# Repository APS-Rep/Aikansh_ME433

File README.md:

# Aikansh_ME433
Repository for ME433 Spring 2022 (Aikansh Prakash Shenoy)

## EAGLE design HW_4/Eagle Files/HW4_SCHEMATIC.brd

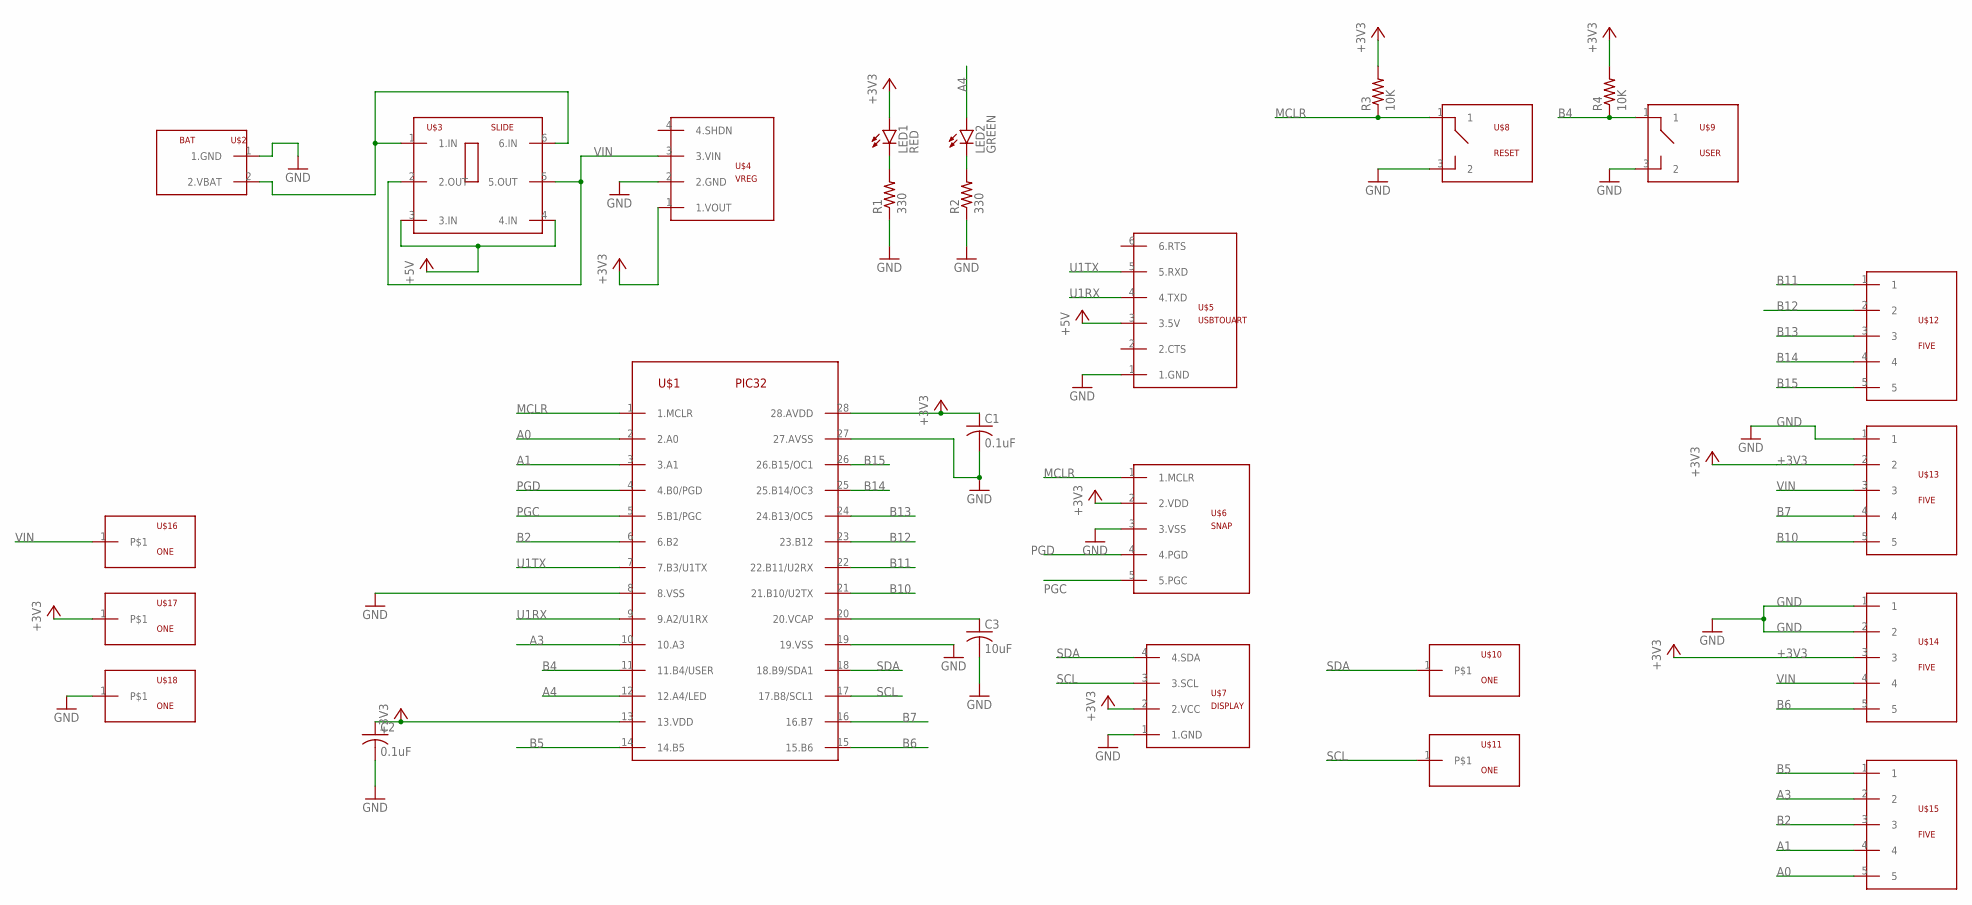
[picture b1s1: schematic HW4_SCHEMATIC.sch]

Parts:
C1, C2: 0.1uF; C025-024X044
C3: 10uF; C025-024X044
LED1: RED; LED3MM
LED2: GREEN; LED3MM
R1, R2: 330; 0207/7
R3, R4: 10K; 0207/7
U$1: PIC32; DIL28-3
U$2: BAT
U$3: SLIDE
U$4: VREG
U$5: USBTOUART
U$6: SNAP
U$7: DISPLAY
U$8: RESET; BUTTON
U$9: USER; BUTTON
U$10, U$11, U$16, U$17, U$18: ONE
U$12, U$13, U$14, U$15: FIVE

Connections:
+3V3: C1.1, C2.1, LED1.A, R3.2, R4.2, U$1.13 (13.VDD), U$1.28 (28.AVDD), U$4.1 (1.VOUT), U$6.2 (2.VDD), U$7.2 (2.VCC), U$13.2, U$14.3, U$17.1
+5V: U$3.3 (3.IN), U$3.4 (4.IN), U$5.3 (3.5V)
A0: U$1.2 (2.A0), U$15.5
A1: U$1.3 (3.A1), U$15.4
A3: U$1.10 (10.A3), U$15.2
A4: LED2.A, U$1.12 (12.A4/LED)
B2: U$1.6 (6.B2), U$15.3
B4: R4.1, U$1.11 (11.B4/USER), U$9.1
B5: U$1.14 (14.B5), U$15.1
B6: U$1.15 (15.B6), U$14.5
B7: U$1.16 (16.B7), U$13.4
B10: U$1.21 (21.B10/U2TX), U$13.5
B11: U$1.22 (22.B11/U2RX), U$12.1
B12: U$1.23 (23.B12), U$12.2
B13: U$1.24 (24.B13/OC5), U$12.3
B14: U$1.25 (25.B14/OC3), U$12.4
B15: U$1.26 (26.B15/OC1), U$12.5
GND: C1.2, C2.2, C3.2, R1.1, R2.1, U$1.8 (8.VSS), U$1.19 (19.VSS), U$1.27 (27.AVSS), U$2.1 (1.GND), U$4.2 (2.GND), U$5.1 (1.GND), U$6.3 (3.VSS), U$7.1 (1.GND), U$8.3 (2), U$9.3 (2), U$13.1, U$14.1, U$14.2, U$18.1
MCLR: R3.1, U$1.1 (1.MCLR), U$6.1 (1.MCLR), U$8.1
unnamed: U$2.2 (2.VBAT), U$3.1 (1.IN), U$3.6 (6.IN)
unnamed: LED2.K (C), R2.2
unnamed: LED1.K (C), R1.2
unnamed: C3.1, U$1.20 (20.VCAP)
PGC: U$1.5 (5.B1/PGC), U$6.5 (5.PGC)
PGD: U$1.4 (4.B0/PGD), U$6.4 (4.PGD)
SCL: U$1.17 (17.B8/SCL1), U$7.3 (3.SCL), U$11.1
SDA: U$1.18 (18.B9/SDA1), U$7.4 (4.SDA), U$10.1
U1RX: U$1.9 (9.A2/U1RX), U$5.4 (4.TXD)
U1TX: U$1.7 (7.B3/U1TX), U$5.5 (5.RXD)
VIN: U$3.2 (2.OUT), U$3.5 (5.OUT), U$4.3 (3.VIN), U$13.3, U$14.4, U$16.1

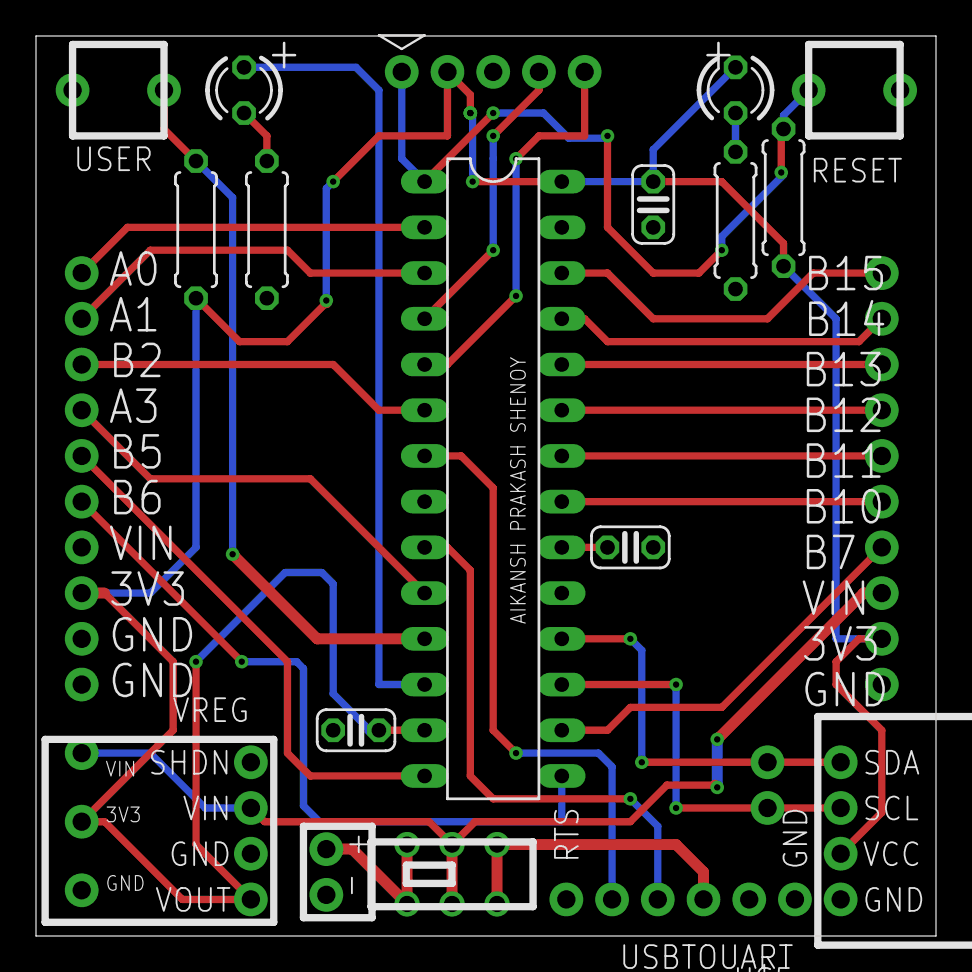
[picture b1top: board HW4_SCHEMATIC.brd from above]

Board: 2 copper layers, 50.0 x 50.0 mm, 27 parts (0 on the bottom side), 30 nets.

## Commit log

2022-06-14 First Push
2022-06-14 Second Push
2022-11-18 Deleting HW5
2022-11-18 HW 5 upload
2022-11-18 Pics Upload
2022-11-22 Pushing HW folders
2022-11-22 HW Folders Push
